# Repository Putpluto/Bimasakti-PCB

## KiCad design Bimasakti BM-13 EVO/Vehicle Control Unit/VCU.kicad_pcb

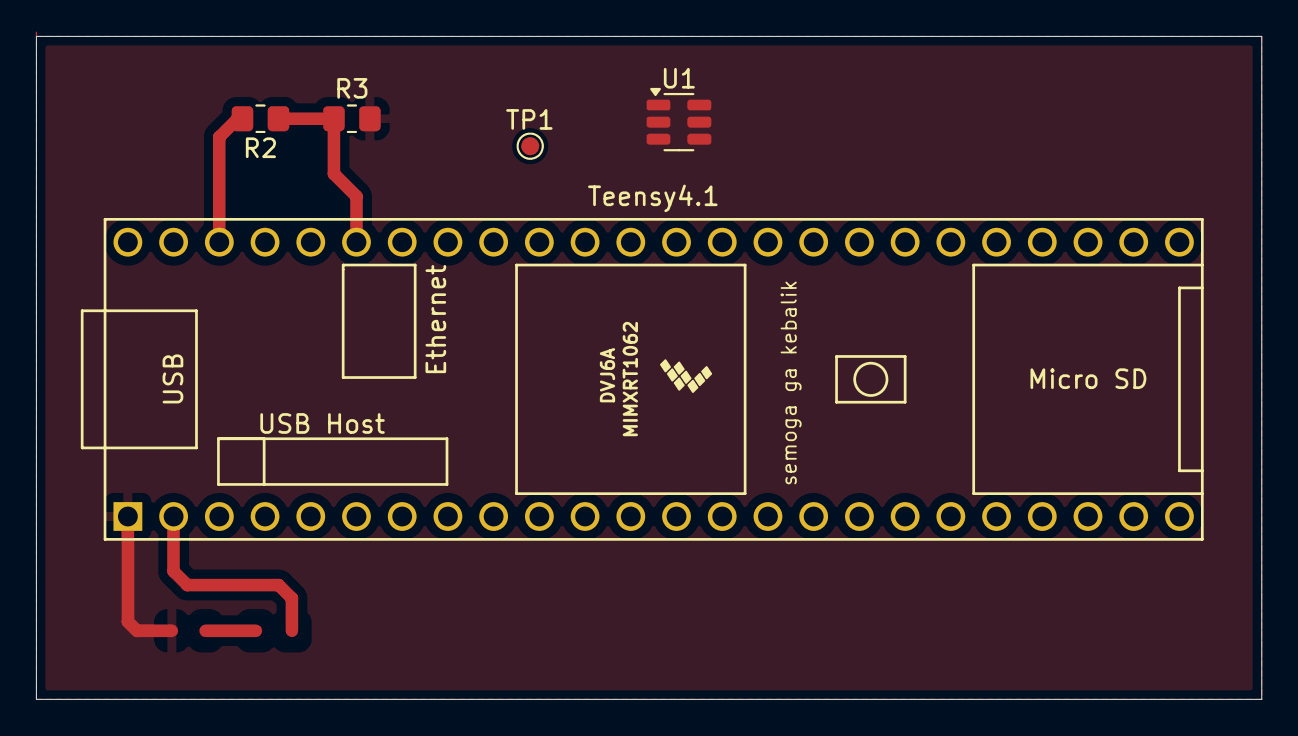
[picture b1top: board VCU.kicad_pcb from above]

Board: 2 copper layers, 68.1 x 36.8 mm, 5 parts (0 on the bottom side), 3 nets.

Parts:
R2, R3: R; R_0805_2012Metric_Pad1.20x1.40mm_HandSolder
TP1: TestPoint; TestPoint_Pad_D1.0mm
Teensy4.1: Teensy41
U1: SRV05-4; SOT-23-6

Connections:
GND: R3.2, U1.2 (VN)
unnamed: R2.2, Teensy4.1.46 (3.3V)
unnamed: R2.1, R3.1, Teensy4.1.43 (A7/RX5)
